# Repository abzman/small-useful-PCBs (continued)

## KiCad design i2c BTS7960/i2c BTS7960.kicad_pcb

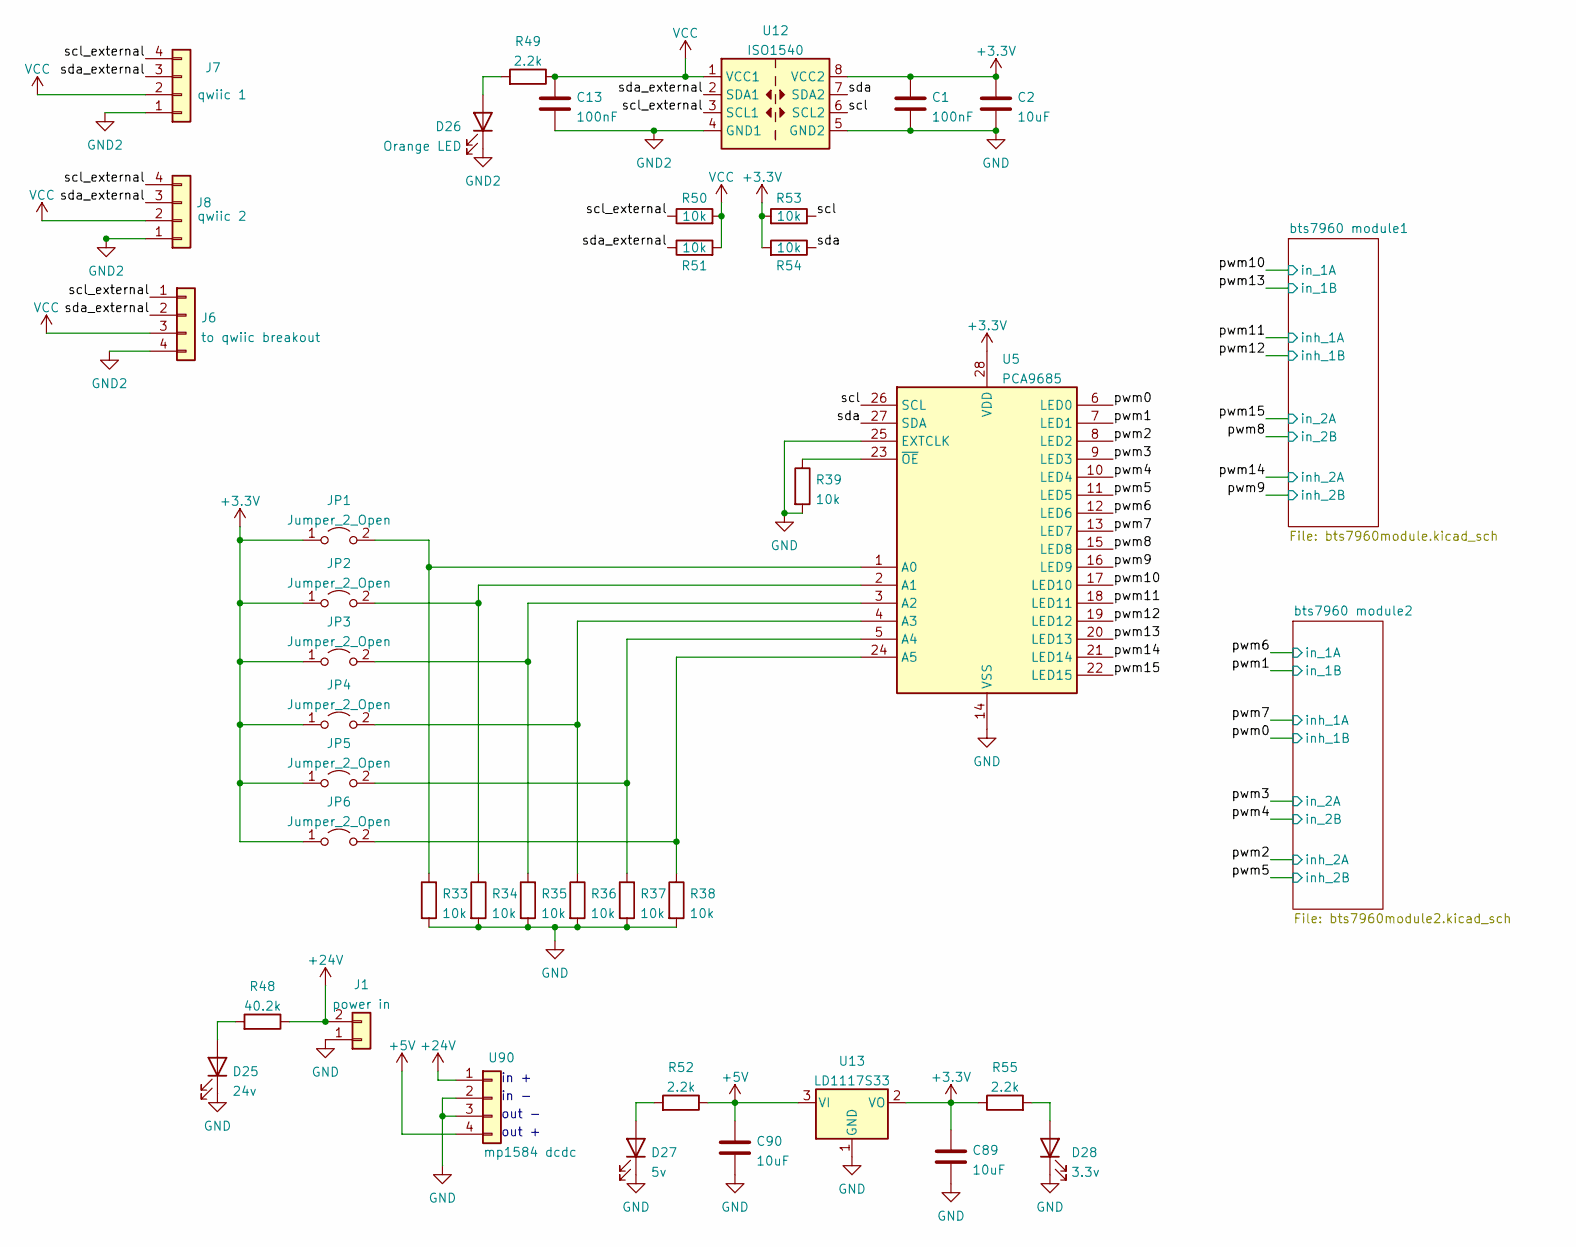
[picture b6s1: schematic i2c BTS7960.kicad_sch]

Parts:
C1, C13: 100nF; C_0603_1608Metric
C2: 10uF; C_0603_1608Metric
C89, C90: 10uF; C_1206_3216Metric
D25: 24v; LED_0603_1608Metric
D26: Orange LED; LED_0603_1608Metric
D27: 5v; LED_0603_1608Metric
D28: 3.3v; LED_0603_1608Metric
J1: power in; TerminalBlock_Phoenix_MKDS-1,5-2_1x02_P5.00mm_Horizontal
J6: to qwiic breakout; PinHeader_1x04_P2.54mm_Vertical
J7: qwiic 1; JST_SH_SM04B-SRSS-TB_1x04-1MP_P1.00mm_Horizontal
J8: qwiic 2; JST_SH_SM04B-SRSS-TB_1x04-1MP_P1.00mm_Horizontal
JP1, JP2, JP3, JP4, JP5: Jumper_2_Open; SolderJumper-2_P1.3mm_Open_RoundedPad1.0x1.5mm
JP6: Jumper_2_Open; SolderJumper-2_P1.3mm_Bridged_RoundedPad1.0x1.5mm
R33, R34, R35, R36, R37, R38, R39, R50, R51, R53, R54: 10k; R_0603_1608Metric
R48: 40.2k; R_0603_1608Metric
R49, R52, R55: 2.2k; R_0603_1608Metric
U5: PCA9685; TSSOP-28_4.4x9.7mm_P0.65mm
U12: ISO1540; SOIC-8_3.9x4.9mm_P1.27mm
U13: LD1117S33; SOT-223-3_TabPin2
U90: mp1584 dcdc; MP1584_buck_module

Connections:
+3V3: C1.1, C2.1, C89.1, JP1.1 (A), JP2.1 (A), JP3.1 (A), JP4.1 (A), JP5.1 (A), JP6.1 (A), R53.2, R54.2, R55.1, U5.28 (VDD), U12.8 (VCC2), U13.2 (VO)
+5V: C90.1, R52.1, U13.3 (VI), U90.4; also elsewhere on the board
+24V: J1.2, R48.1, U90.1; also elsewhere on the board
/pwm0: U5.6 (LED0); also elsewhere on the board
/pwm1: U5.7 (LED1); also elsewhere on the board
/pwm2: U5.8 (LED2); also elsewhere on the board
/pwm3: U5.9 (LED3); also elsewhere on the board
/pwm4: U5.10 (LED4); also elsewhere on the board
/pwm5: U5.11 (LED5); also elsewhere on the board
/pwm6: U5.12 (LED6); also elsewhere on the board
/pwm7: U5.13 (LED7); also elsewhere on the board
/pwm8: U5.15 (LED8); also elsewhere on the board
/pwm9: U5.16 (LED9); also elsewhere on the board
/pwm10: U5.17 (LED10); also elsewhere on the board
/pwm11: U5.18 (LED11); also elsewhere on the board
/pwm12: U5.19 (LED12); also elsewhere on the board
/pwm13: U5.20 (LED13); also elsewhere on the board
/pwm14: U5.21 (LED14); also elsewhere on the board
/pwm15: U5.22 (LED15); also elsewhere on the board
/scl: R53.1, U5.26 (SCL), U12.6 (SCL2)
/scl_external: J6.1, J7.4, J8.4, R50.1, U12.3 (SCL1)
/sda: R54.1, U5.27 (SDA), U12.7 (SDA2)
/sda_external: J6.2, J7.3, J8.3, R51.1, U12.2 (SDA1)
GND: C1.2, C2.2, C89.2, C90.2, D25.1 (K), D27.1 (K), D28.1 (K), J1.1, R33.2, R34.2, R35.2, R36.2, R37.2, R38.2, R39.2, U5.14 (VSS), U5.25 (EXTCLK), U12.5 (GND2), U13.1 (GND), U90.2, U90.3; also elsewhere on the board
GND2: C13.2, D26.1 (K), J6.4, J7.1, J8.1, U12.4 (GND1)
unnamed: D25.2 (A), R48.2
unnamed: D26.2 (A), R49.2
unnamed: D27.2 (A), R52.2
unnamed: D28.2 (A), R55.2
unnamed: JP1.2 (B), R33.1, U5.1 (A0)
unnamed: JP2.2 (B), R34.1, U5.2 (A1)
unnamed: JP3.2 (B), R35.1, U5.3 (A2)
unnamed: JP4.2 (B), R36.1, U5.4 (A3)
unnamed: JP5.2 (B), R37.1, U5.5 (A4)
unnamed: JP6.2 (B), R38.1, U5.24 (A5)
unnamed: R39.1, U5.23 (~OE)
VCC: C13.1, J6.3, J7.2, J8.2, R49.1, R50.2, R51.2, U12.1 (VCC1)

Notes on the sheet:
in +
out -
out +
in -

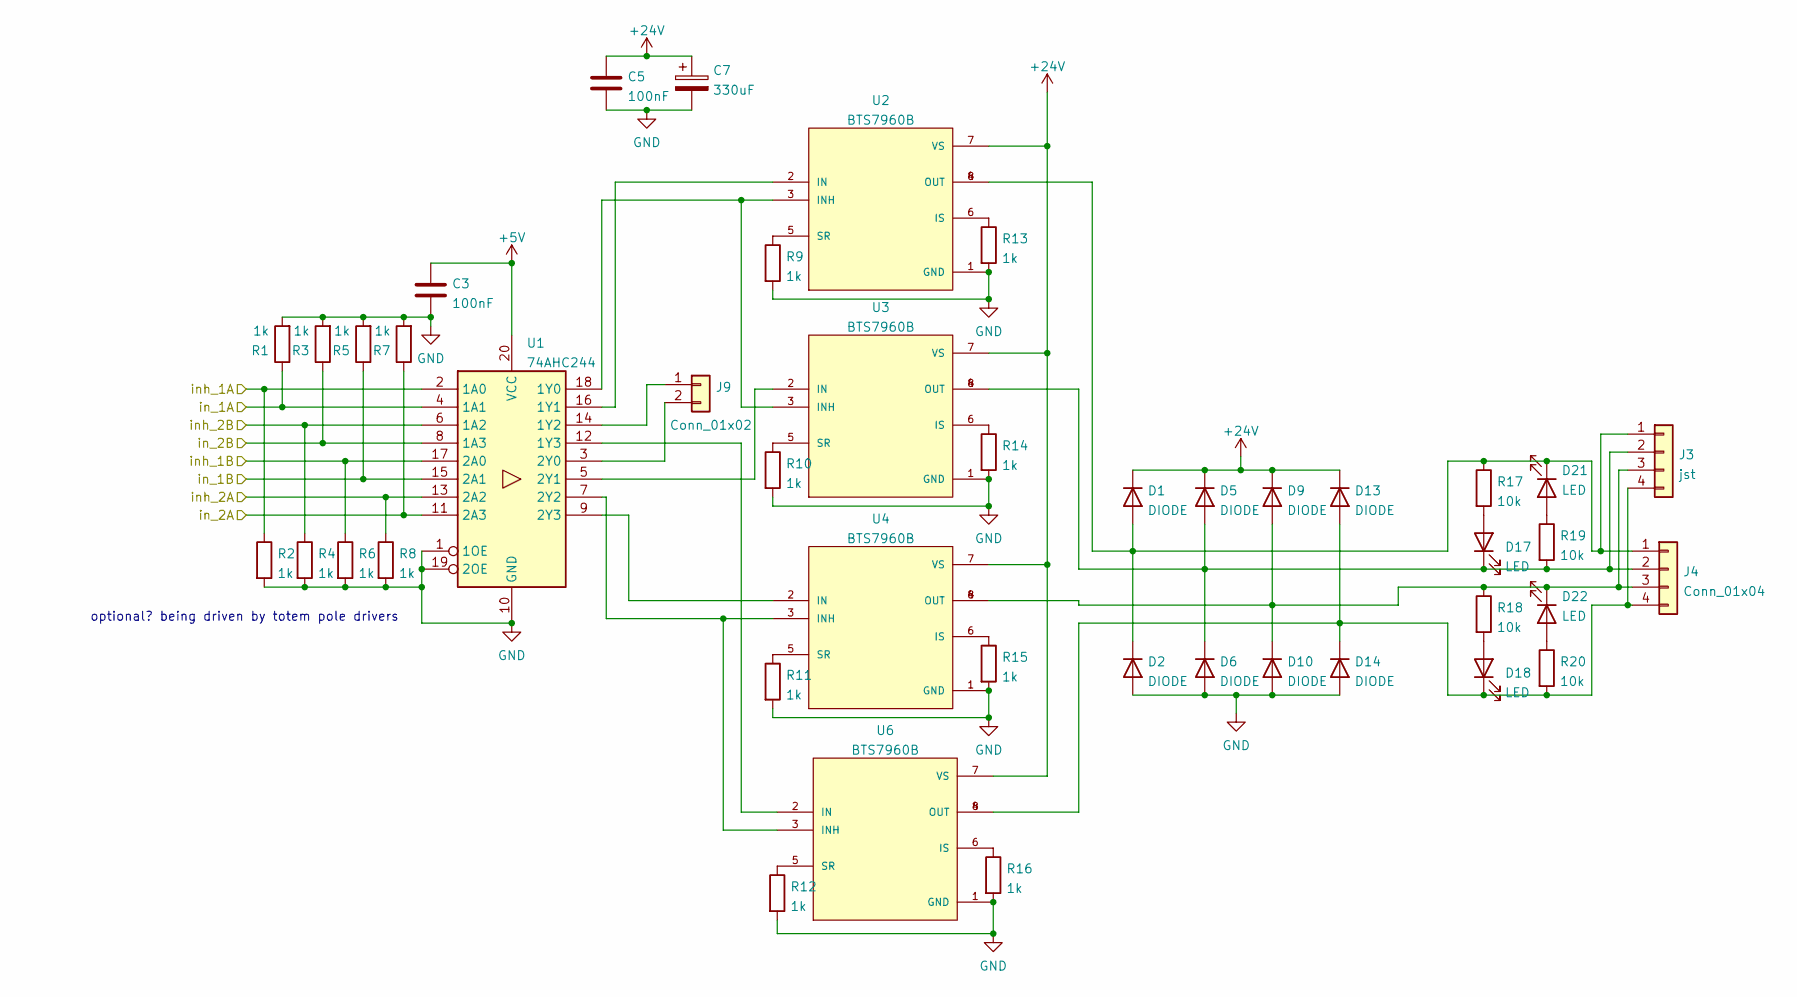
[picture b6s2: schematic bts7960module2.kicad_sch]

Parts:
C3, C5: 100nF; C_0603_1608Metric
C7: 330uF; CP_Radial_D10.0mm_P5.00mm
D1, D2, D5, D6, D9, D10, D13, D14: DIODE; D_SMA
D17, D18, D21, D22: LED; LED_0603_1608Metric
J3: jst; JST_XH_B4B-XH-A_1x04_P2.50mm_Vertical
J4: Conn_01x04; TerminalBlock_Phoenix_MKDS-1,5-4_1x04_P5.00mm_Horizontal
J9: Conn_01x02; PinHeader_2x01_P2.54mm_Vertical
R1, R2, R3, R4, R5, R6, R7, R8, R9, R10, R11, R12, R13, R14, R15, R16: 1k; R_0603_1608Metric
R17, R18, R19, R20: 10k; R_0603_1608Metric
U1: 74AHC244; SOIC-20W_7.5x12.8mm_P1.27mm
U2, U3, U4, U6: BTS7960B; DPAK127P1490X440-8N; PARTREV 1.1

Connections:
+5V: C3.1, U1.20 (VCC); also elsewhere on the board
+24V: C5.1, C7.1, D1.2 (K), D5.2 (K), D9.2 (K), D13.2 (K), U2.7 (VS), U3.7 (VS), U4.7 (VS), U6.7 (VS); also elsewhere on the board
/pwm0: R6.1, U1.17 (2A0); also elsewhere on the board
/pwm1: R5.1, U1.15 (2A1); also elsewhere on the board
/pwm2: R8.1, U1.13 (2A2); also elsewhere on the board
/pwm3: R7.1, U1.11 (2A3); also elsewhere on the board
/pwm4: R3.1, U1.8 (1A3); also elsewhere on the board
/pwm5: R4.1, U1.6 (1A2); also elsewhere on the board
/pwm6: R1.1, U1.4 (1A1); also elsewhere on the board
/pwm7: R2.1, U1.2 (1A0); also elsewhere on the board
GND: C3.2, C5.2, C7.2, D2.1 (A), D6.1 (A), D10.1 (A), D14.1 (A), R1.2, R2.2, R3.2, R4.2, R5.2, R6.2, R7.2, R8.2, R9.2, R10.2, R11.2, R12.2, R13.2, R14.2, R15.2, R16.2, U1.1 (1OE), U1.10 (GND), U1.19 (2OE), U2.1 (GND), U3.1 (GND), U4.1 (GND), U6.1 (GND); also elsewhere on the board
unnamed: D1.1 (A), D2.2 (K), D21.1 (K), J3.1, J4.1, R17.1, U2.4 (OUT), U2.8 (OUT)
unnamed: D9.1 (A), D10.2 (K), D22.1 (K), J3.3, J4.3, R18.1, U4.4 (OUT), U4.8 (OUT)
unnamed: D13.1 (A), D14.2 (K), D18.1 (K), J3.4, J4.4, R20.2, U6.4 (OUT), U6.8 (OUT)
unnamed: D5.1 (A), D6.2 (K), D17.1 (K), J3.2, J4.2, R19.2, U3.4 (OUT), U3.8 (OUT)
unnamed: D17.2 (A), R17.2
unnamed: D18.2 (A), R18.2
unnamed: D21.2 (A), R19.1
unnamed: D22.2 (A), R20.1
unnamed: R9.1, U2.5 (SR)
unnamed: R10.1, U3.5 (SR)
unnamed: R11.1, U4.5 (SR)
unnamed: R12.1, U6.5 (SR)
unnamed: R13.1, U2.6 (IS)
unnamed: R14.1, U3.6 (IS)
unnamed: R15.1, U4.6 (IS)
unnamed: R16.1, U6.6 (IS)
unnamed: J9.2, U1.3 (2Y0)
unnamed: U1.5 (2Y1), U3.2 (IN)
unnamed: U1.7 (2Y2), U4.3 (INH), U6.3 (INH)
unnamed: U1.9 (2Y3), U4.2 (IN)
unnamed: U1.12 (1Y3), U6.2 (IN)
unnamed: J9.1, U1.14 (1Y2)
unnamed: U1.16 (1Y1), U2.2 (IN)
unnamed: U1.18 (1Y0), U2.3 (INH), U3.3 (INH)

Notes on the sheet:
optional? being driven by totem pole drivers

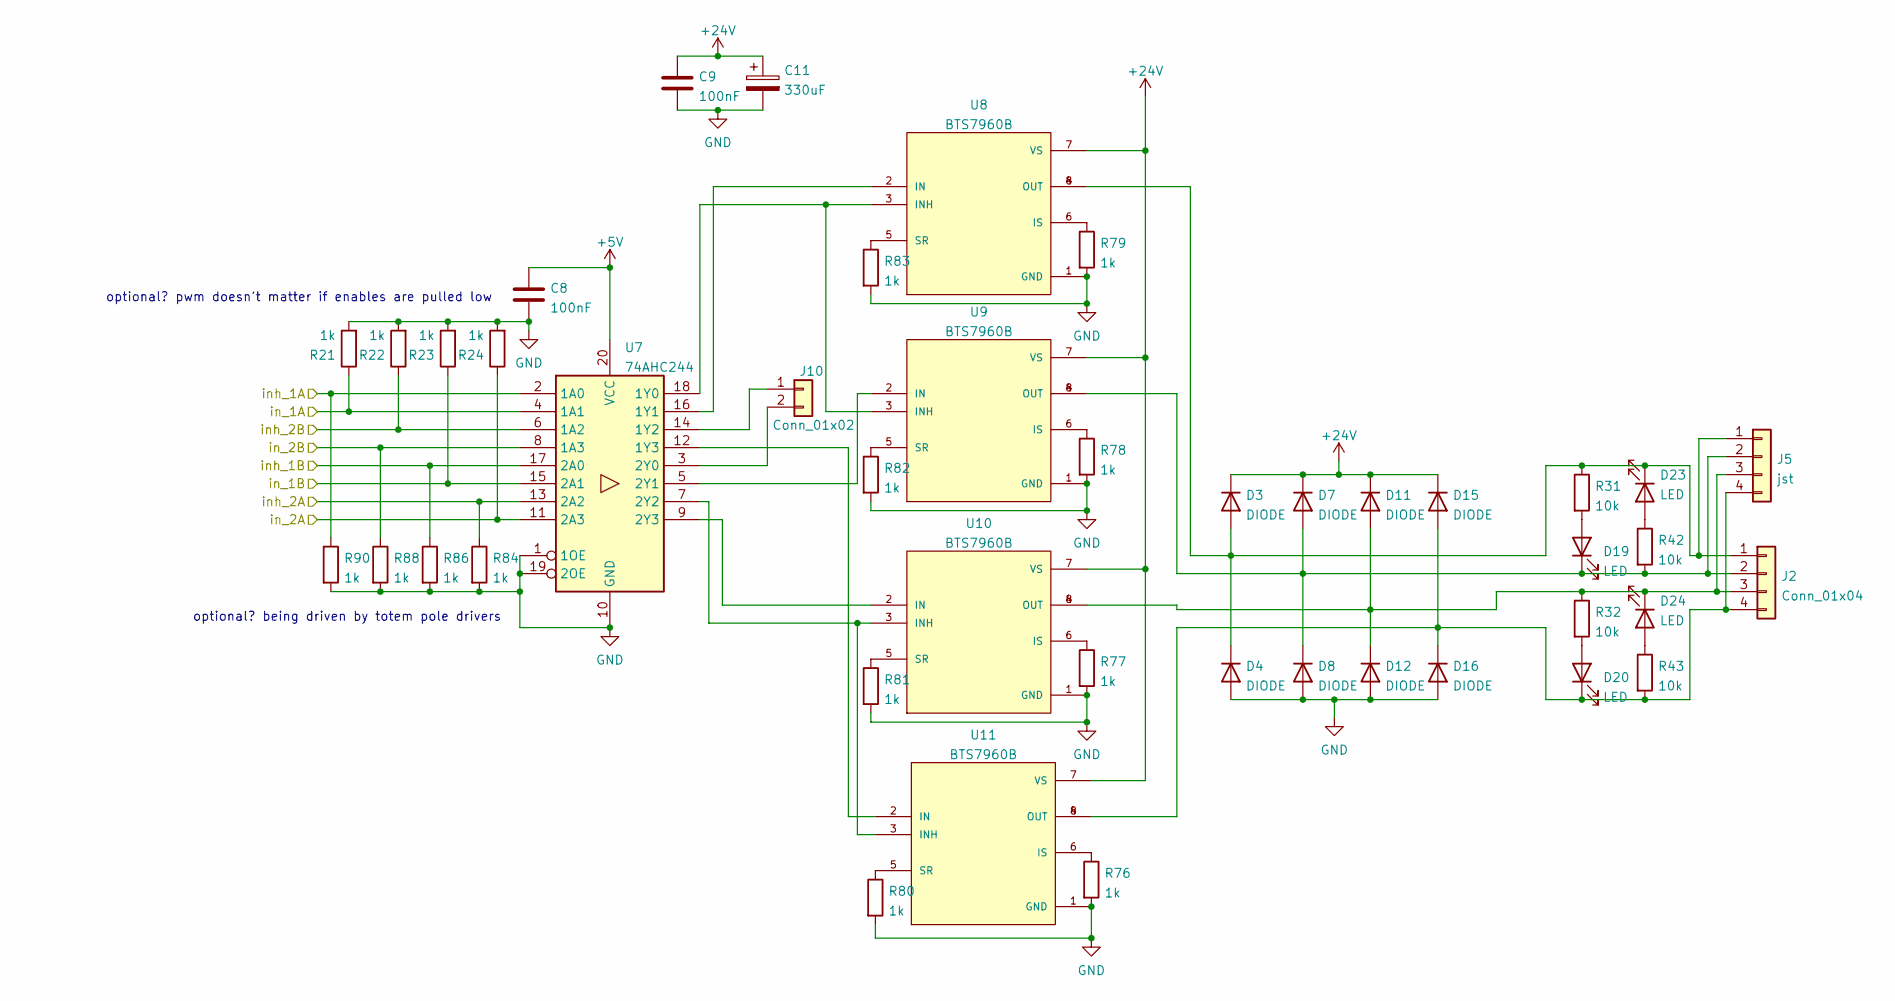
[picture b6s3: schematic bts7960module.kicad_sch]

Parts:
C8, C9: 100nF; C_0603_1608Metric
C11: 330uF; CP_Radial_D10.0mm_P5.00mm
D3, D4, D7, D8, D11, D12, D15, D16: DIODE; D_SMA
D19, D20, D23, D24: LED; LED_0603_1608Metric
J2: Conn_01x04; TerminalBlock_Phoenix_MKDS-1,5-4_1x04_P5.00mm_Horizontal
J5: jst; JST_XH_B4B-XH-A_1x04_P2.50mm_Vertical
J10: Conn_01x02; PinHeader_2x01_P2.54mm_Vertical
R21, R22, R23, R24, R76, R77, R78, R79, R80, R81, R82, R83, R84, R86, R88, R90: 1k; R_0603_1608Metric
R31, R32, R42, R43: 10k; R_0603_1608Metric
U7: 74AHC244; SOIC-20W_7.5x12.8mm_P1.27mm
U8, U9, U10, U11: BTS7960B; DPAK127P1490X440-8N; PARTREV 1.1

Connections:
+5V: C8.1, U7.20 (VCC); also elsewhere on the board
+24V: C9.1, C11.1, D3.2 (K), D7.2 (K), D11.2 (K), D15.2 (K), U8.7 (VS), U9.7 (VS), U10.7 (VS), U11.7 (VS); also elsewhere on the board
/pwm8: R88.1, U7.8 (1A3); also elsewhere on the board
/pwm9: R22.1, U7.6 (1A2); also elsewhere on the board
/pwm10: R21.1, U7.4 (1A1); also elsewhere on the board
/pwm11: R90.1, U7.2 (1A0); also elsewhere on the board
/pwm12: R86.1, U7.17 (2A0); also elsewhere on the board
/pwm13: R23.1, U7.15 (2A1); also elsewhere on the board
/pwm14: R84.1, U7.13 (2A2); also elsewhere on the board
/pwm15: R24.1, U7.11 (2A3); also elsewhere on the board
GND: C8.2, C9.2, C11.2, D4.1 (A), D8.1 (A), D12.1 (A), D16.1 (A), R21.2, R22.2, R23.2, R24.2, R76.2, R77.2, R78.2, R79.2, R80.2, R81.2, R82.2, R83.2, R84.2, R86.2, R88.2, R90.2, U7.1 (1OE), U7.10 (GND), U7.19 (2OE), U8.1 (GND), U9.1 (GND), U10.1 (GND), U11.1 (GND); also elsewhere on the board
unnamed: D11.1 (A), D12.2 (K), D24.1 (K), J2.3, J5.3, R32.1, U10.4 (OUT), U10.8 (OUT)
unnamed: D15.1 (A), D16.2 (K), D20.1 (K), J2.4, J5.4, R43.2, U11.4 (OUT), U11.8 (OUT)
unnamed: D7.1 (A), D8.2 (K), D19.1 (K), J2.2, J5.2, R42.2, U9.4 (OUT), U9.8 (OUT)
unnamed: D19.2 (A), R31.2
unnamed: D20.2 (A), R32.2
unnamed: D3.1 (A), D4.2 (K), D23.1 (K), J2.1, J5.1, R31.1, U8.4 (OUT), U8.8 (OUT)
unnamed: D23.2 (A), R42.1
unnamed: D24.2 (A), R43.1
unnamed: R76.1, U11.6 (IS)
unnamed: R77.1, U10.6 (IS)
unnamed: R78.1, U9.6 (IS)
unnamed: R79.1, U8.6 (IS)
unnamed: R80.1, U11.5 (SR)
unnamed: R81.1, U10.5 (SR)
unnamed: R82.1, U9.5 (SR)
unnamed: R83.1, U8.5 (SR)
unnamed: J10.2, U7.3 (2Y0)
unnamed: U7.5 (2Y1), U9.2 (IN)
unnamed: J10.1, U7.14 (1Y2)
unnamed: U7.16 (1Y1), U8.2 (IN)
unnamed: U7.18 (1Y0), U8.3 (INH), U9.3 (INH)
unnamed: U7.9 (2Y3), U10.2 (IN)
unnamed: U7.7 (2Y2), U10.3 (INH), U11.3 (INH)
unnamed: U7.12 (1Y3), U11.2 (IN)

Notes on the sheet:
optional? pwm doesn't matter if enables are pulled low
optional? being driven by totem pole drivers

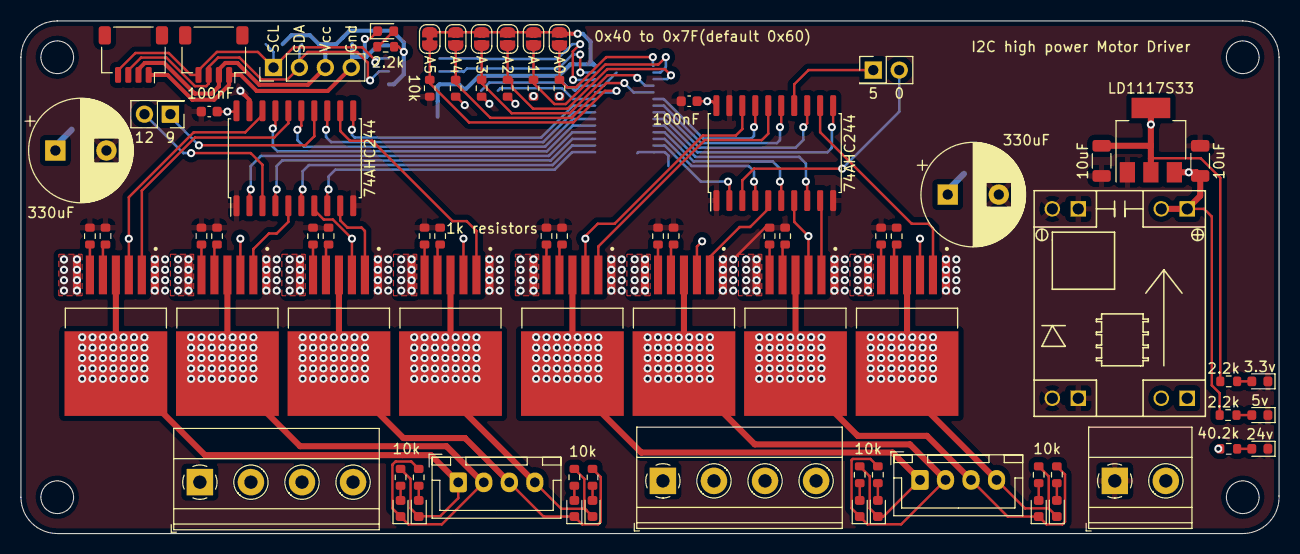
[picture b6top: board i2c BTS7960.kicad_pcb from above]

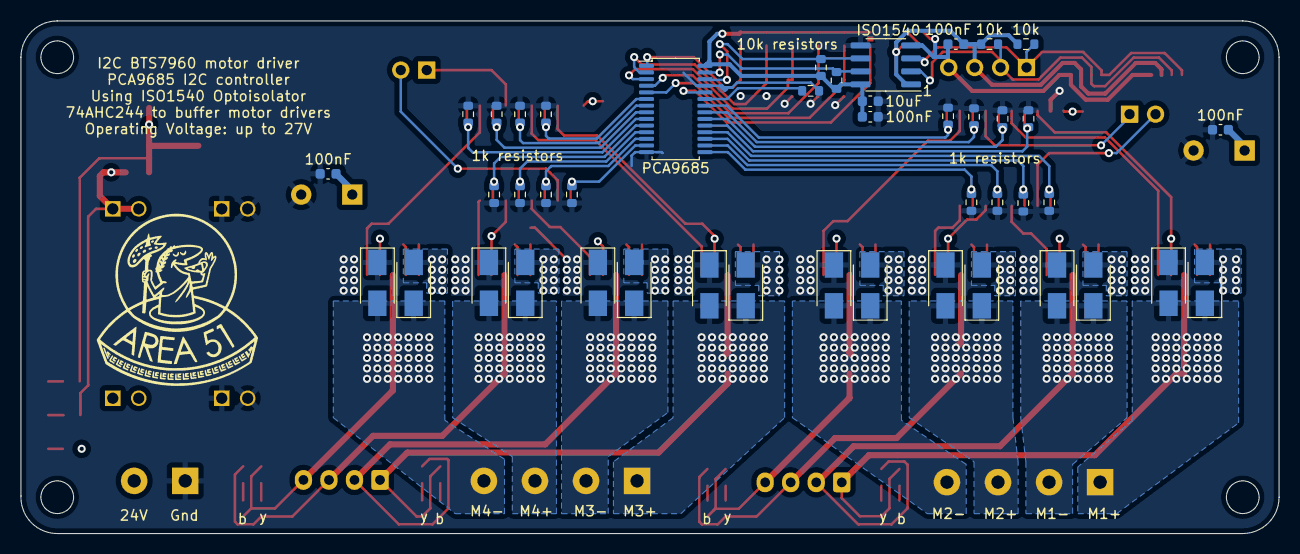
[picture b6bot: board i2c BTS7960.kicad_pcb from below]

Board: 4 copper layers, 123.2 x 50.2 mm, 124 parts (44 on the bottom side), 85 nets.

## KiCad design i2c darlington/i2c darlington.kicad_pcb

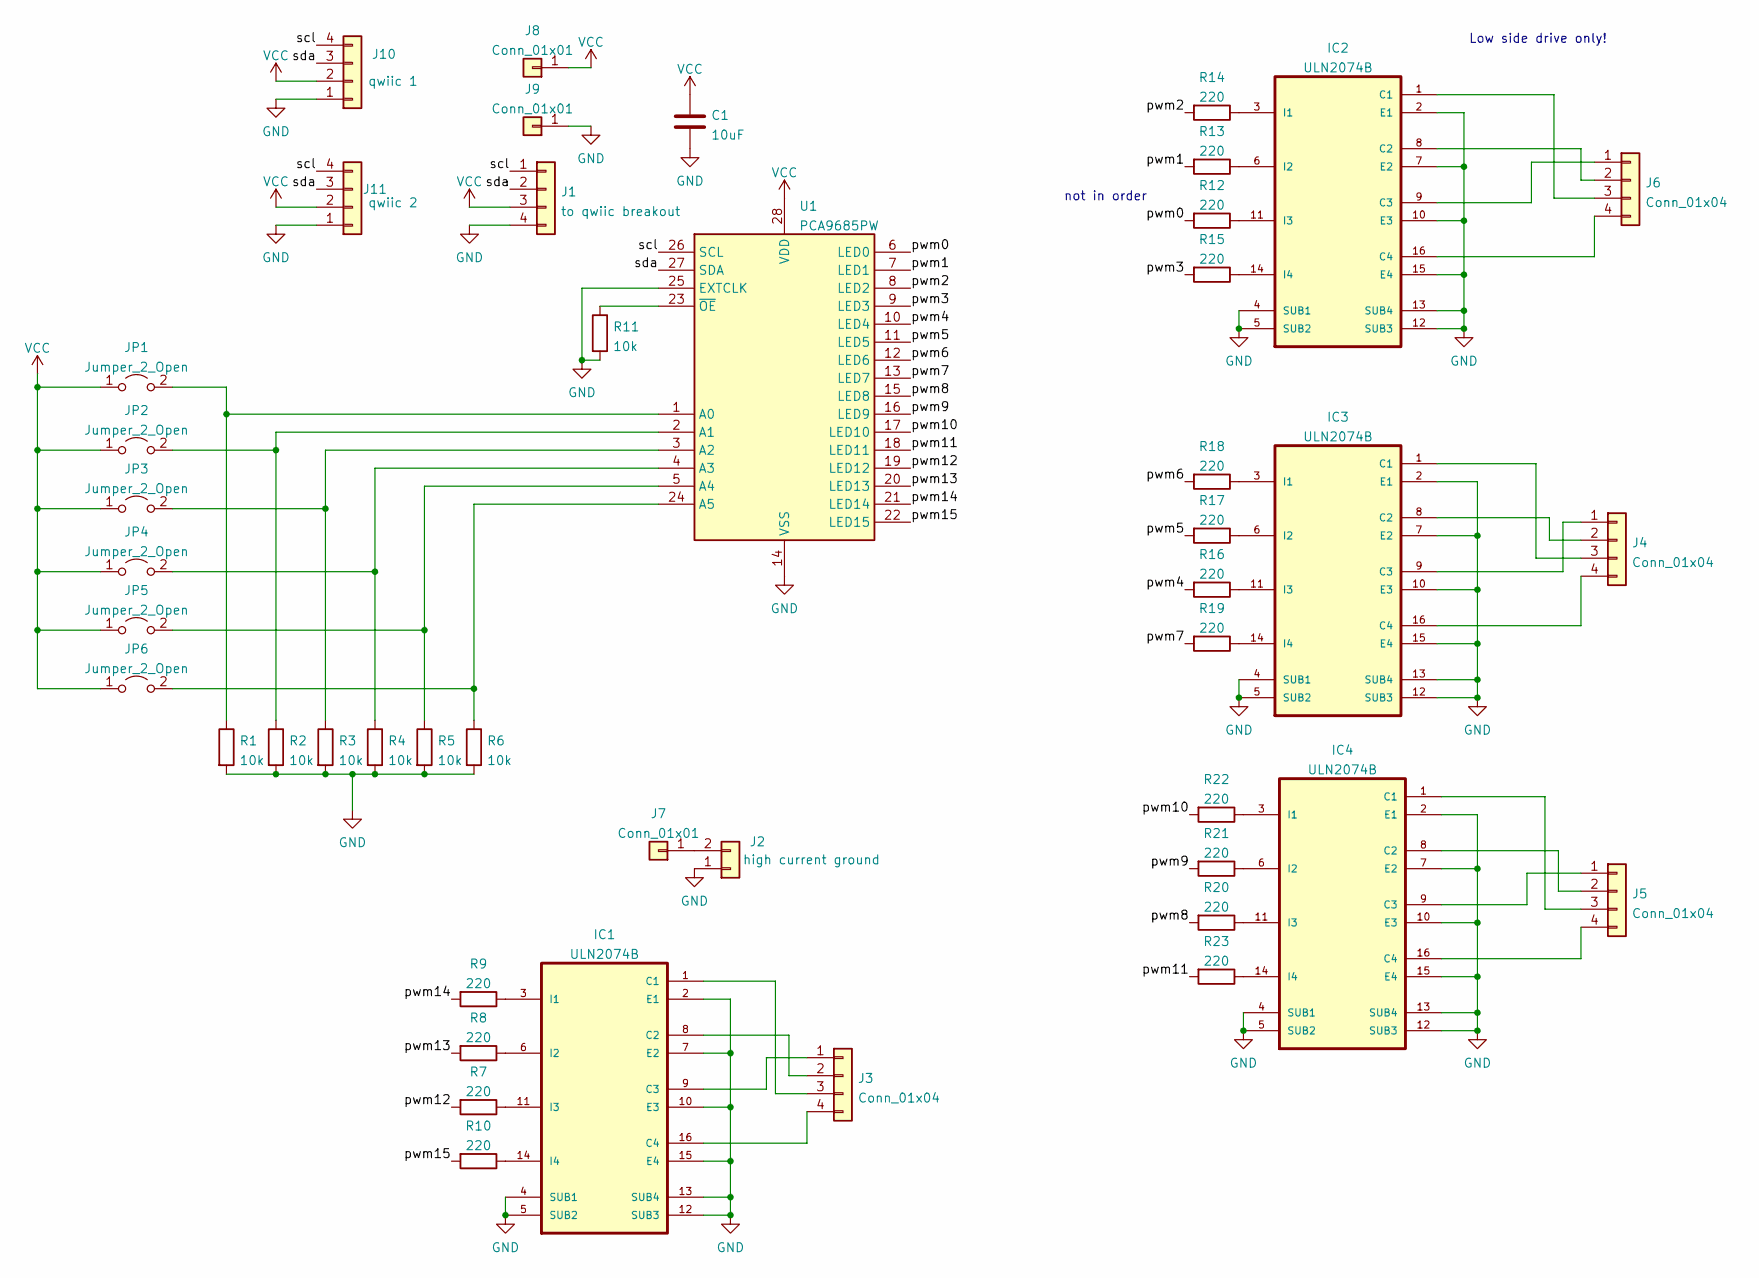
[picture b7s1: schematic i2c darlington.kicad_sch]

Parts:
C1: 10uF; C_0603_1608Metric
IC1, IC2, IC3, IC4: ULN2074B; DIP-16_W7.62mm
J1: to qwiic breakout; PinHeader_1x04_P2.54mm_Vertical
J2: high current ground; TerminalBlock_Phoenix_MKDS-1,5-2_1x02_P5.00mm_Horizontal
J3, J4, J5, J6: Conn_01x04; TerminalBlock_Phoenix_MKDS-1,5-4_1x04_P5.00mm_Horizontal
J7, J8, J9: Conn_01x01; PinHeader_1x01_P2.54mm_Vertical
J10: qwiic 1; JST_SH_SM04B-SRSS-TB_1x04-1MP_P1.00mm_Horizontal
J11: qwiic 2; JST_SH_SM04B-SRSS-TB_1x04-1MP_P1.00mm_Horizontal
JP1, JP2, JP3, JP4, JP5, JP6: Jumper_2_Open; SolderJumper-2_P1.3mm_Open_RoundedPad1.0x1.5mm
R1, R2, R3, R4, R5, R6, R11: 10k; R_0603_1608Metric
R7, R8, R9, R10, R12, R13, R14, R15, R16, R17, R18, R19, R20, R21, R22, R23: 220; R_0603_1608Metric
U1: PCA9685PW; TSSOP-28_4.4x9.7mm_P0.65mm

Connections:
/pwm0: R12.2, U1.6 (LED0)
/pwm1: R13.2, U1.7 (LED1)
/pwm2: R14.2, U1.8 (LED2)
/pwm3: R15.2, U1.9 (LED3)
/pwm4: R16.2, U1.10 (LED4)
/pwm5: R17.2, U1.11 (LED5)
/pwm6: R18.2, U1.12 (LED6)
/pwm7: R19.2, U1.13 (LED7)
/pwm8: R20.2, U1.15 (LED8)
/pwm9: R21.2, U1.16 (LED9)
/pwm10: R22.2, U1.17 (LED10)
/pwm11: R23.2, U1.18 (LED11)
/pwm12: R7.2, U1.19 (LED12)
/pwm13: R8.2, U1.20 (LED13)
/pwm14: R9.2, U1.21 (LED14)
/pwm15: R10.2, U1.22 (LED15)
/scl: J1.1, J10.4, J11.4, U1.26 (SCL)
/sda: J1.2, J10.3, J11.3, U1.27 (SDA)
GND: C1.2, IC1.2 (E1), IC1.4 (SUB1), IC1.5 (SUB2), IC1.7 (E2), IC1.10 (E3), IC1.12 (SUB3), IC1.13 (SUB4), IC1.15 (E4), IC2.2 (E1), IC2.4 (SUB1), IC2.5 (SUB2), IC2.7 (E2), IC2.10 (E3), IC2.12 (SUB3), IC2.13 (SUB4), IC2.15 (E4), IC3.2 (E1), IC3.4 (SUB1), IC3.5 (SUB2), IC3.7 (E2), IC3.10 (E3), IC3.12 (SUB3), IC3.13 (SUB4), IC3.15 (E4), IC4.2 (E1), IC4.4 (SUB1), IC4.5 (SUB2), IC4.7 (E2), IC4.10 (E3), IC4.12 (SUB3), IC4.13 (SUB4), IC4.15 (E4), J1.4, J2.1, J9.1, J10.1, J11.1, R1.2, R2.2, R3.2, R4.2, R5.2, R6.2, R11.2, U1.14 (VSS), U1.25 (EXTCLK)
unnamed: IC1.1 (C1), J3.3
unnamed: IC1.3 (I1), R9.1
unnamed: IC1.6 (I2), R8.1
unnamed: IC1.8 (C2), J3.2
unnamed: IC1.9 (C3), J3.1
unnamed: IC1.11 (I3), R7.1
unnamed: IC1.14 (I4), R10.1
unnamed: IC1.16 (C4), J3.4
unnamed: IC2.1 (C1), J6.3
unnamed: IC2.3 (I1), R14.1
unnamed: IC2.6 (I2), R13.1
unnamed: IC2.8 (C2), J6.2
unnamed: IC2.9 (C3), J6.1
unnamed: IC2.11 (I3), R12.1
unnamed: IC2.14 (I4), R15.1
unnamed: IC2.16 (C4), J6.4
unnamed: IC3.1 (C1), J4.3
unnamed: IC3.3 (I1), R18.1
unnamed: IC3.6 (I2), R17.1
unnamed: IC3.8 (C2), J4.2
unnamed: IC3.9 (C3), J4.1
unnamed: IC3.11 (I3), R16.1
unnamed: IC3.14 (I4), R19.1
unnamed: IC3.16 (C4), J4.4
unnamed: IC4.1 (C1), J5.3
unnamed: IC4.3 (I1), R22.1
unnamed: IC4.6 (I2), R21.1
unnamed: IC4.8 (C2), J5.2
unnamed: IC4.9 (C3), J5.1
unnamed: IC4.11 (I3), R20.1
unnamed: IC4.14 (I4), R23.1
unnamed: IC4.16 (C4), J5.4
unnamed: J2.2, J7.1
unnamed: JP1.2 (B), R1.1, U1.1 (A0)
unnamed: JP2.2 (B), R2.1, U1.2 (A1)
unnamed: JP3.2 (B), R3.1, U1.3 (A2)
unnamed: JP4.2 (B), R4.1, U1.4 (A3)
unnamed: JP5.2 (B), R5.1, U1.5 (A4)
unnamed: JP6.2 (B), R6.1, U1.24 (A5)
unnamed: R11.1, U1.23 (~OE)
VCC: C1.1, J1.3, J8.1, J10.2, J11.2, JP1.1 (A), JP2.1 (A), JP3.1 (A), JP4.1 (A), JP5.1 (A), JP6.1 (A), U1.28 (VDD)

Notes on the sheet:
Low side drive only!
not in order

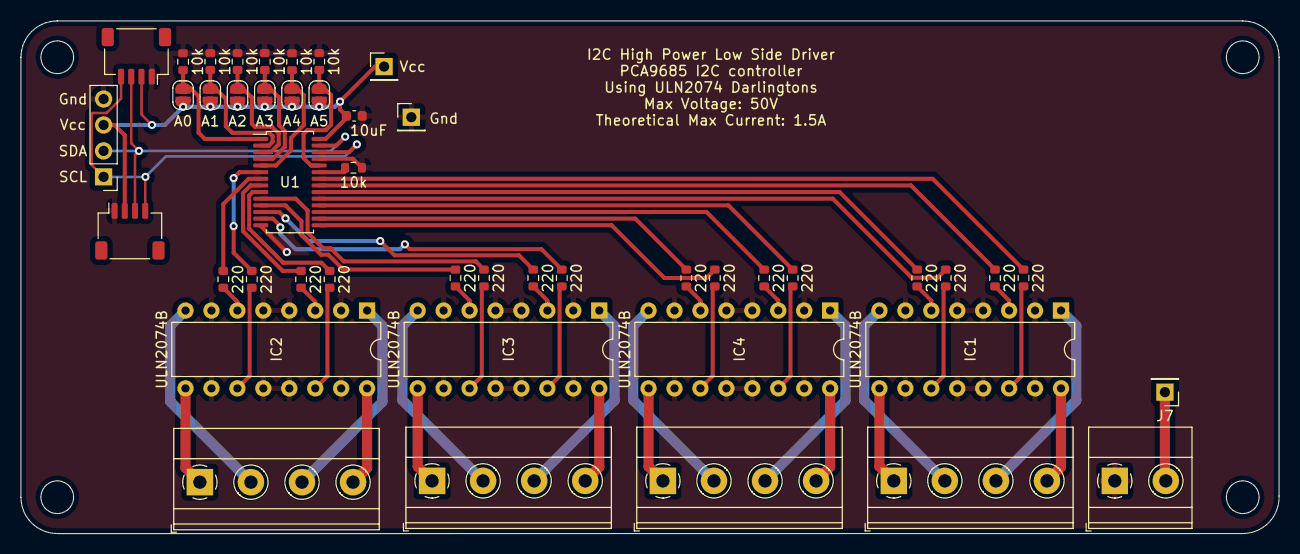
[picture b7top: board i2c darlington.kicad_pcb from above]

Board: 2 copper layers, 123.2 x 50.2 mm, 46 parts (0 on the bottom side), 60 nets.
